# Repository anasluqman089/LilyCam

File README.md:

# LilyCam

LilyCam is a custom DIY digital camera built from scratch around the Seeed Studio XIAO ESP32-S3 Sense, a tiny, low-cost microcontroller board with an integrated camera sensor and microSD card slot inspired by the Kodak Charmera Keychain

The idea behind the name

"Lily" evokes something small, elegant, and blooming. A compact camera that fits in your palm but still delivers personality through its built-in creative filters making photography playful and personal.

## What it does
Core Features :

Button	Function

SW1 — Power	Toggles the camera between active mode and deep sleep (ultra-low battery drain)

SW2 — Shutter	Captures a photo and saves it to the microSD card

SW3 — Style	Cycles creative color filters: Normal → Grayscale → Negative → Sepia → Night Vision Green

## BOM

| Item | Qty | Part Name | Description | Price (\$) | Product Page Link |
| :---: | :---: | :--- | :--- | :---: | :--- |
| **1** | 1 | Seeed Studio XIAO ESP32-S3 Sense | Dual-core ESP32-S3 MCU with detachable OV2640 camera board and digital mic | \$13.90 | [Seeed Studio Product Page](https://www.seeedstudio.com/XIAO-ESP32S3-Sense-p-5639.html) |
| **2** | 3 | 6mm Tactile Switch (6x6x5mm) | 4-pin momentary push button for hardware input/reset | \$1.00 | Search target: `6x6x5mm tactile switch pack` |
| **3** | 1 | 1.3 Inch TFT IPS Display Module | 240x240 Full-Color Screen with SPI interface (ST7789 Driver) | \$7.99 | [Amazon Product Page](https://www.amazon.com/Display-Module-240x240-Interface-Arduino/dp/B0DN9NMBFW/ref=sr_1_10) |

### Note
* **PCB and 3D printing**: PCB and 3D printind doesnt included in the Bill of material. 
* **Buttons (Tactile Switches)**: These are universally sold in multi-packs (usually 10 to 50 pieces) rather than single units, which accounts for the \$1.00 baseline package price. 
* **Display Interface**: The 1.3-inch screen utilizes a **4-wire SPI communication interface** driven by the **ST7789** controller chip. Ensure you match the pinout labels (GND, VCC, SCL, SDA, RES, DC, BLK) to the corresponding digital pins on your XIAO module during assembly.

## Schematics

## PCB

## CAD

## Extra
This project is made for Hack Club YSWS program : Stardance
Links : https://stardance.hackclub.com/projects/59421

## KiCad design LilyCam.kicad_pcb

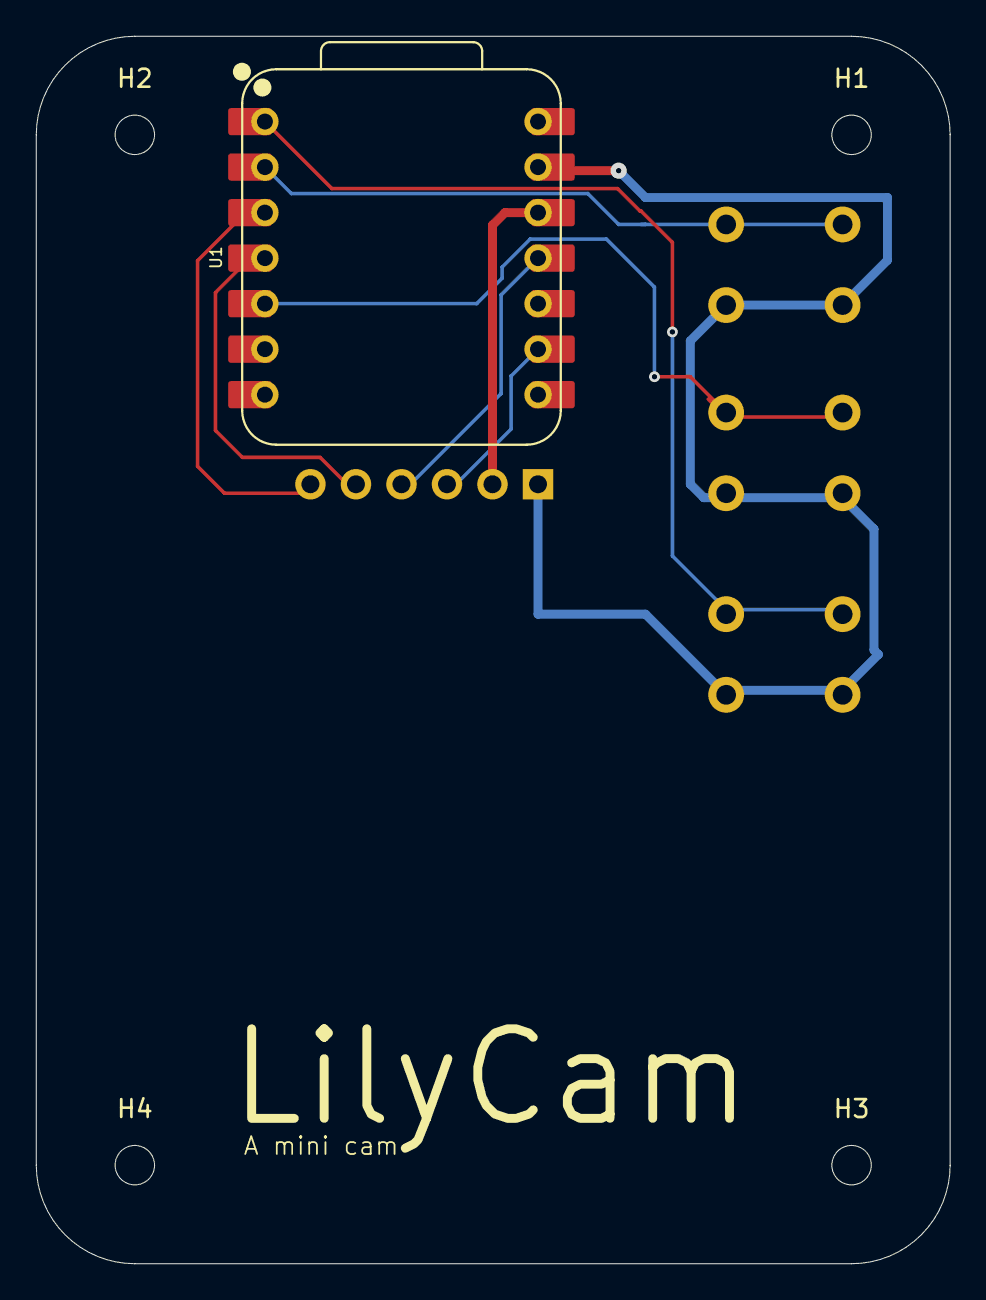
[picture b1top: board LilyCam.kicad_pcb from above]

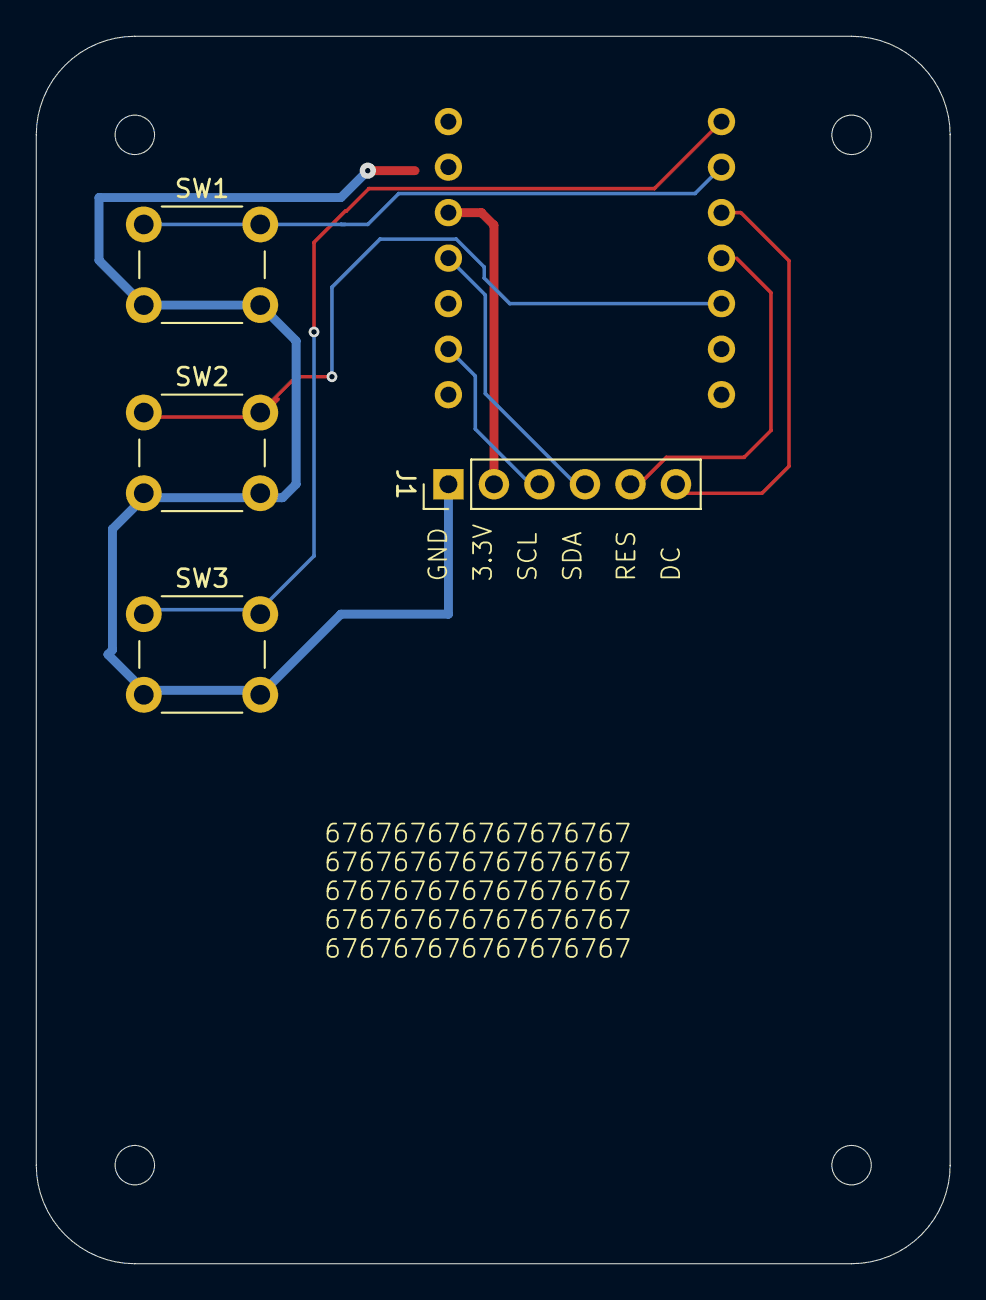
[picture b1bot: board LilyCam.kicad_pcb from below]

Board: 2 copper layers, 51.0 x 68.5 mm, 9 parts (4 on the bottom side), 9 nets.

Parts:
H1, H2, H3, H4: MountingHole; MountingHole_2.2mm_M2
J1: Conn_01x06_Socket; PinHeader_1x06_P2.54mm_Vertical
SW1, SW2, SW3: SW_Push; SW_PUSH_6mm
U1: XIAO-ESP32-S3-SMD; XIAO-ESP32-S3-DIP

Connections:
+3.3V: J1.2, U1.12 (3V3_OUT)
/1: SW3.1, U1.1 (D0)
/2: SW1.1, U1.2 (D1)
/3: SW2.1, U1.5 (D4)
/DC: J1.6, U1.3 (D2)
/RES: J1.5, U1.4 (D3)
/SCL: J1.3, U1.9 (D8)
/SDA: J1.4, U1.11 (D10)
GND: J1.1, SW1.2, SW2.2, SW3.2, U1.13 (GND)
